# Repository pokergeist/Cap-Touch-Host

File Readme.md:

# Cap Touch Host Project

## Introduction

This project provides two board designs supporting capacitive touch sensing. The host board supports up to (4) cap touch sensor modules using Microchip's [CAP1188](https://www.digikey.com/en/products/detail/microchip-technology/CAP1188-1-CP-TR/3871672) IC ([datasheet](https://ww1.microchip.com/downloads/en/DeviceDoc/00001620C.pdf)) supporting (32) capacitive touch surfaces . A 5th Adafruit CAP1188 board could be used by connecting it to the MCU's Qwiic/STEMMA QT port with 5V to the VIN pin.

## The Sensor Board

The sensor board is similar to Adafruit's CAP1188 ([#1602)](https://www.adafruit.com/product/1602) board, but without level-shifting, LEDs, and access to the WAKE and ALERT pins. The ADDR_COMM and RESET pins are routed to the host board. The I2C pull-up resistors have been moved to the host board since four of five sensor modules could be in parallel, plus EEPROM or other components.. The LDO voltage regulator chip has been left on-board for better power distribution.

It should be noted that there are no pull-up resistors for the CAP1188's LED driver, so the LED drive mode will have to be changed from "open-drain" to "push-pull" mode. The output logic level can be inverted to provide a positive signal to trigger solid state relays requiring positive logic.

The default LED drive mode is open-drain such that when a switch is triggered, an n-channel MOSFET is turned-on switching the MOSFET drain and LED cathode to ground, illuminating the LED since its anode is pulled high.

The Cap Sensor inputs (CS1-8) and LED outputs (LED1-8) are not routed through the host board. Outputs can be wired directly from the sensor board when needed - otherwise, switch status can be read from the status registers via I2C.

### Schematic

### Parts List

| Component |            Description             | Quan. |                         Part Number                          | Notes |
| :-------: | :--------------------------------: | :---: | :----------------------------------------------------------: | ----- |
|    U1     |      Cap Touch Sensor 24VQFN       |   1   | Microchip [CAP1188-1-CP-TR](https://www.digikey.com/short/jdhph3bp) |       |
|    U2     | LDO 3V3 Voltage Regulator SOT-23-5 |   1   | Microchip [MIC5225-3.3YM5-TR](https://www.digikey.com/short/h5855rbn) |       |

2x4 and 2x5 headers and housings may be useful. Through-hole pattern: 0.1" pitch, 0.040" holes.

##  The Host Board

The host board provides a microcontroller (MCU), Adafruit QT Py SAMD21 ([#4600](https://www.adafruit.com/product/4600)) and I2C EEPROM IC, and hosts (4) Sensor boards. It provides 5V power via the USB-C pc-host or charging cable, and 3.3V I2C pull-up via the MCU's 3V3 voltage regulator.

Each of the RESET lines is pulled high and controlled by the MCU so that the MCU can make configuration changes immediately after dropping the RESET line to a logic low.

Each of the sensor module's ADDR_COMM pins are set to a different I2C address. U3 (module #1) uses the default address of 0x28. Address 0x29 (program resistor = 150kΩ) is available so that an unmodified Adafruit CAP1188 module can be attached via the QT Py MCU's Qwiic/STEMMA QT port. I2C addresses are printed on the PC board and schematic.

### Host Board Schematic

### Parts List

| Component |          Description          | Quan.  |                         Part Number                          | Notes                          |
| :-------: | :---------------------------: | :----: | :----------------------------------------------------------: | ------------------------------ |
|    U1     |       QT PY SAMD21 MCU        |   1    |   Adafruit [#4600](https://www.digikey.com/short/b2fc2jh4)   | Microcontroller                |
|    U2     |  IC EEPROM 32KBIT I2C 8-SOIC  |   1    | ON Semi [CAT24C32WI-GT3](https://www.digikey.com/short/5h0p7b04) | EEPROM memory for config.      |
|    RA1    | RES ARRAY 4 RES 6.8K OHM 1206 |  1 *   | Bourns [CAT16-682J4LF](https://www.digikey.com/short/hrmr0547) | RESET pull-ups.                |
|  R1, R2   |    RES 3.3kΩ 5% 1/4W 1206     |   2    | Stackpole [RMCF1206JT3K30](https://www.digikey.com/short/57h2z201) | I2C pull-ups.                  |
|    R4     |    RES 120kΩ 1% 1/4W 1206     | 0 or 1 | Stackpole [RMCF1206FT120K](https://www.digikey.com/short/3tnptfrc) | Sets I2C address of module O4. |
|    R5     |    RES 100kΩ 1% 1/4W 1206     | 0 or 1 | Stackpole [RMCF1206FT100K](https://www.digikey.com/short/2pfhhrhr) | Sets I2C address of module U5. |
|    R6     |     RES 82kΩ 1% 1/4W 1206     | 0 or 1 | Stackpole [RMCF1206FT82K0](https://www.digikey.com/short/r0n5dq3d) | Sets I2C address of module U6. |

**Note**:

* Resistor array RA1  may not be necessary if:
  *  the GPIO lines default to a weak-pull-up INPUT mode or
  * you don't care that the **FIXME** ???
*  there's no pull-down resistor on the RESET pin of this sensor module. (10kΩ pull-down on the Adafruit board.)
* There is no resistor R3 since the address programming resistor was removed to allow use with an Adafruit CAP1188 board.

## FIXME - Add notes on RESTART, LED Drive, Invert, ...

## Status

|    Date    | Status                                                       |
| :--------: | ------------------------------------------------------------ |
| 2023-04-04 | Posted board files.                                          |
| 2023-03-13 | Posted to GitHub.                                            |
| 2023-03-12 | Concept posted to ATMakers FB [group](https://www.facebook.com/groups/ATMakers). |

No one in the target group has an immediate need for theses boards so none are being procured at the moment. Hence there's been no testing of a delivered product or software.

## Todo

* Create board markdown files.

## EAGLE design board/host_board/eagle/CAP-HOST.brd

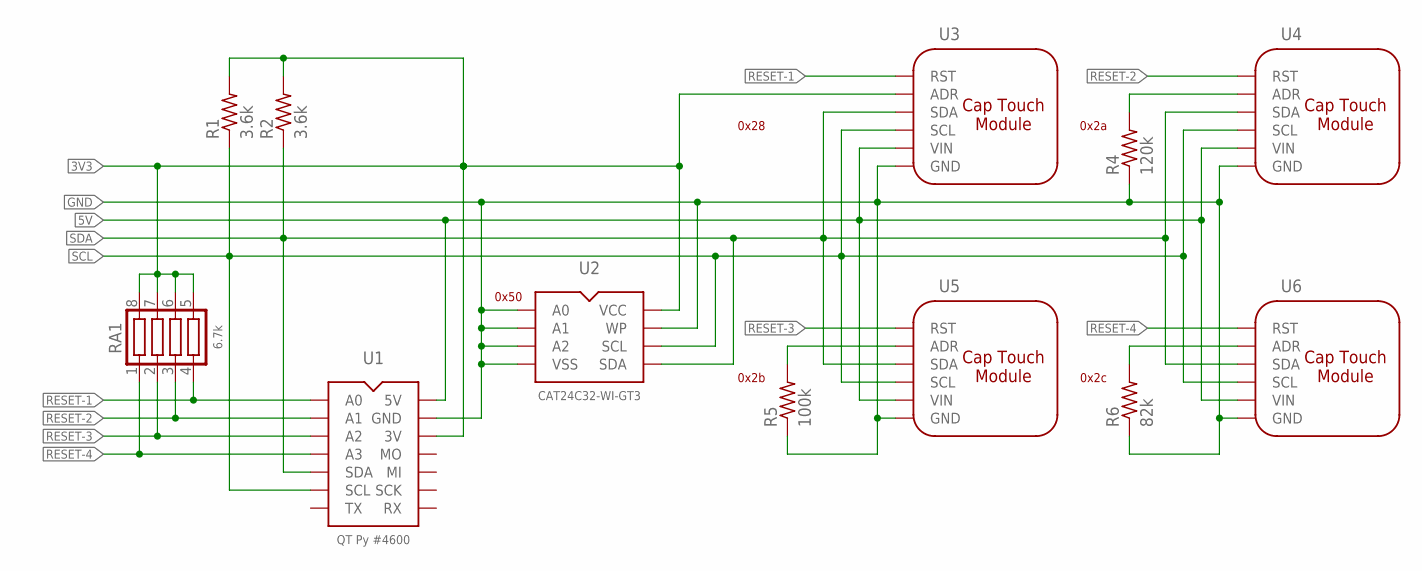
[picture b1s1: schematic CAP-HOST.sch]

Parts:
R1, R2: 3.6k; R1206
R4: 120k; R1206
R5: 100k; R1206
R6: 82k; R1206
RA1: 6.7k; RES-NET-1206
U1: QT Py #4600; QT_PY-CASTL
U2: CAT24C32-WI-GT3; SOIC-8-ON
U3, U4, U5, U6: CAP-SENSOR-INTF; CAP-TOUCH-MODULE-2

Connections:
3V3: R1.2, R2.2, RA1.5, RA1.6, RA1.7, RA1.8, U1.3V3 (3V), U2.P$8 (VCC), U3.ADR
5V: U1.5V, U3.VIN, U4.VIN, U5.VIN, U6.VIN
GND: R4.1, R5.1, R6.1, U1.GND, U2.P$1 (A0), U2.P$2 (A1), U2.P$3 (A2), U2.P$4 (VSS), U2.P$7 (WP), U3.GND, U4.GND, U5.GND, U6.GND
unnamed: R5.2, U5.ADR
unnamed: R6.2, U6.ADR
unnamed: R4.2, U4.ADR
RESET-1: RA1.4, U1.A0, U3.RST
RESET-2: RA1.3, U1.A1, U4.RST
RESET-3: RA1.2, U1.A2, U5.RST
RESET-4: RA1.1, U1.A3, U6.RST
SCL: R1.1, U1.SCL, U2.P$6 (SCL), U3.SCL, U4.SCL, U5.SCL, U6.SCL
SDA: R2.1, U1.SDA, U2.P$5 (SDA), U3.SDA, U4.SDA, U5.SDA, U6.SDA

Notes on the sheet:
0x28
0x2a
0x2c
0x2b
0x50

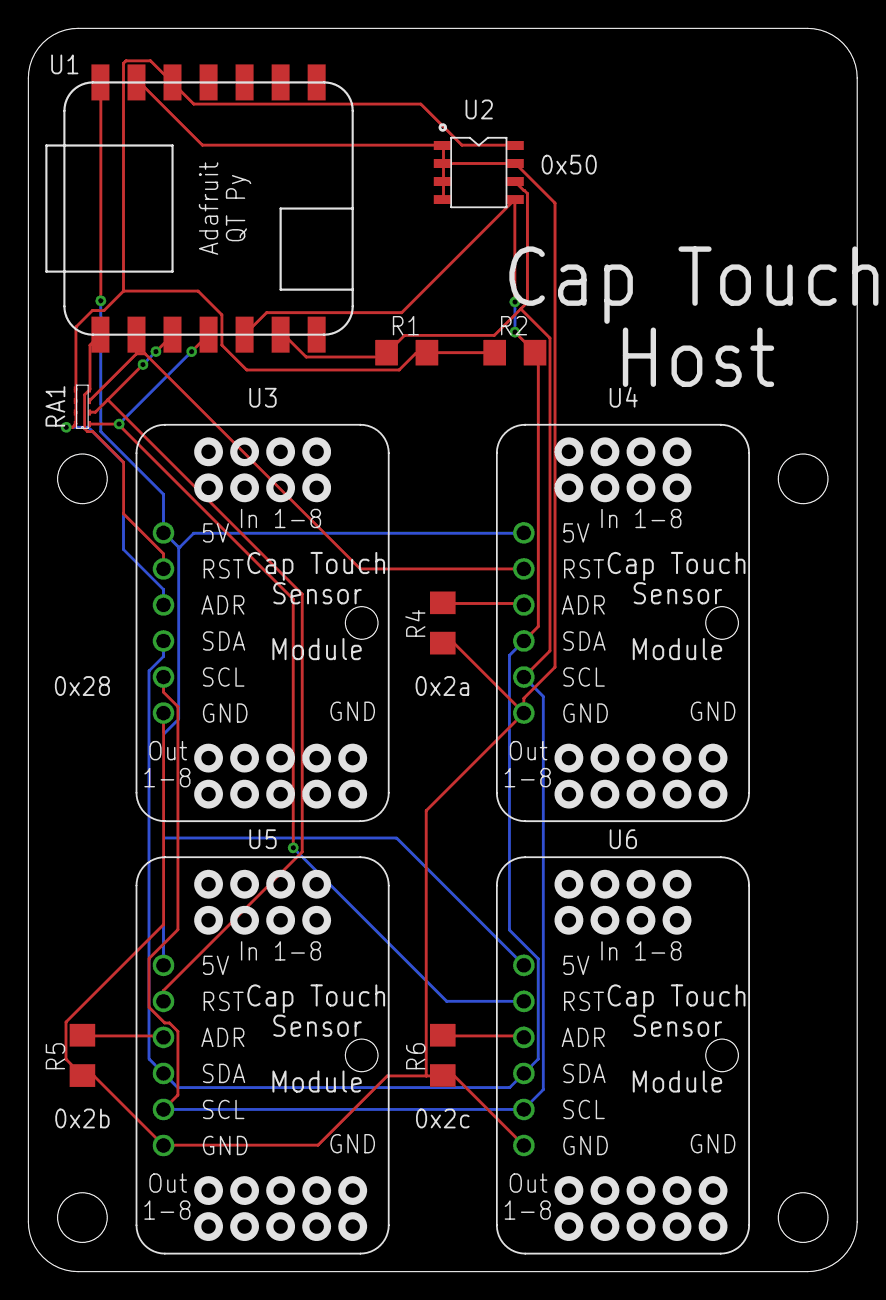
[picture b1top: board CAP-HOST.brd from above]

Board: 2 copper layers, 58.4 x 87.6 mm, 12 parts (0 on the bottom side), 12 nets.

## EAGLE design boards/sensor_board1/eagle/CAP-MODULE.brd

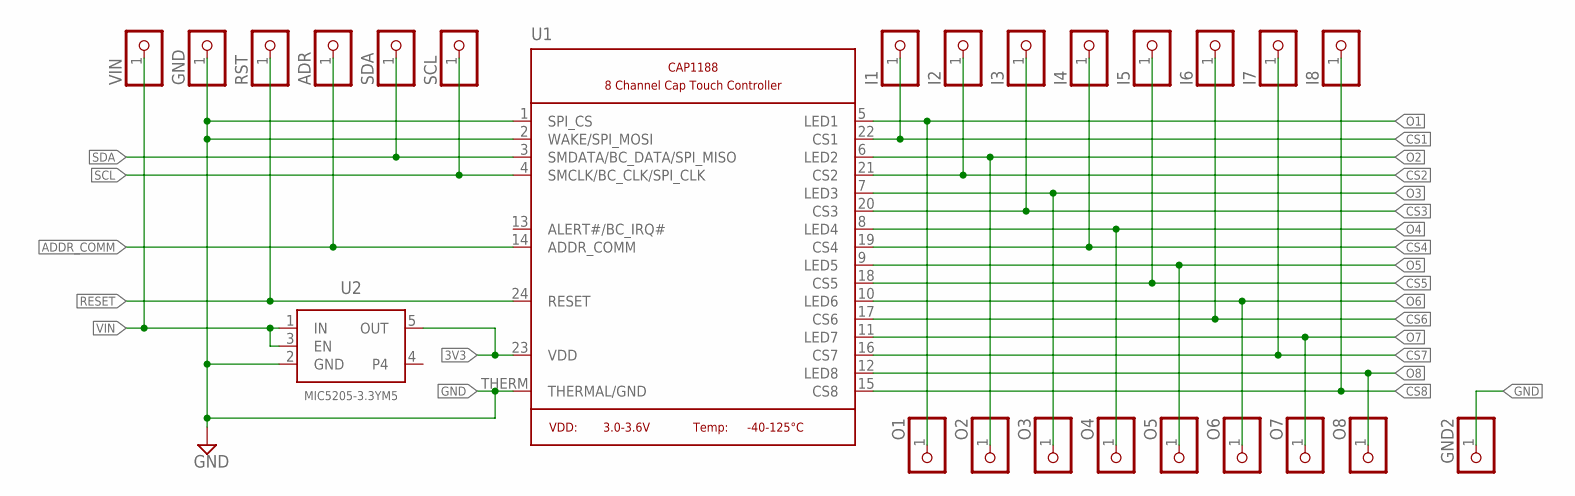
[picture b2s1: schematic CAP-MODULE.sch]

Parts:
ADR: PINHD-1X1CB; 1X01-CLEANBIG
GND, GND2: PINHD-1X1CB; 1X01-CLEANBIG
I1, I2, I3, I4, I5, I6, I7, I8: PINHD-1X1CB; 1X01-CLEANBIG
O1, O2, O3, O4, O5, O6, O7, O8: PINHD-1X1CB; 1X01-CLEANBIG
RST: PINHD-1X1CB; 1X01-CLEANBIG
SCL: PINHD-1X1CB; 1X01-CLEANBIG
SDA: PINHD-1X1CB; 1X01-CLEANBIG
U1: MICROBUILDER_CAP1188; MICROBUILDER_QFN24_4MM_SMSC
U2: MIC5205-3.3YM5; MICROBUILDER_SOT23-5
VIN: PINHD-1X1CB; 1X01-CLEANBIG

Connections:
3V3: U1.23 (VDD), U2.5 (OUT)
ADDR_COMM: ADR.1, U1.14 (ADDR_COMM)
CS1: I1.1, U1.22 (CS1)
CS2: I2.1, U1.21 (CS2)
CS3: I3.1, U1.20 (CS3)
CS4: I4.1, U1.19 (CS4)
CS5: I5.1, U1.18 (CS5)
CS6: I6.1, U1.17 (CS6)
CS7: I7.1, U1.16 (CS7)
CS8: I8.1, U1.15 (CS8)
GND: GND.1, GND2.1, U1.1 (SPI_CS), U1.2 (WAKE/SPI_MOSI), U1.THERM (THERMAL/GND), U2.2 (GND)
O1: O1.1, U1.5 (LED1)
O2: O2.1, U1.6 (LED2)
O3: O3.1, U1.7 (LED3)
O4: O4.1, U1.8 (LED4)
O5: O5.1, U1.9 (LED5)
O6: O6.1, U1.10 (LED6)
O7: O7.1, U1.11 (LED7)
O8: O8.1, U1.12 (LED8)
RESET: RST.1, U1.24 (RESET)
SCL: SCL.1, U1.4 (SMCLK/BC_CLK/SPI_CLK)
SDA: SDA.1, U1.3 (SMDATA/BC_DATA/SPI_MISO)
VIN: U2.1 (IN), U2.3 (EN), VIN.1

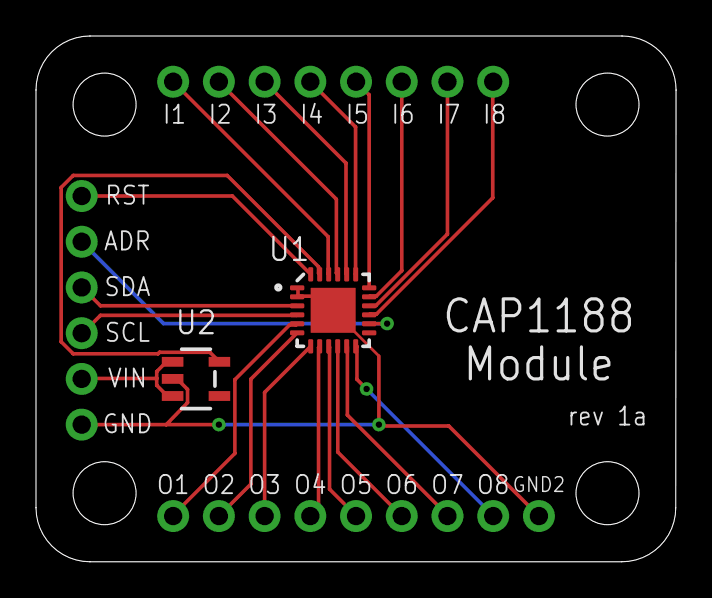
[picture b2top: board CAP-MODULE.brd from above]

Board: 2 copper layers, 35.6 x 29.2 mm, 25 parts (0 on the bottom side), 23 nets.

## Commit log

2023-03-14 path /
2023-04-04 eagle board files & readme
2023-04-04 and the host board
2023-04-04 fixed dir path
2023-04-04 board readme files
2023-04-04 fixed img links
